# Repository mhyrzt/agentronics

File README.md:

# agentronics
Revisiting electronics and embedded systems with old sparks, new circuits, questionable ideas, and a few AI agents running around the lab with a suspicious amount of confidence.

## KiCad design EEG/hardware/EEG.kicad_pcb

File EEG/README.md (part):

# Building a four-channel EEG: from electrodes to wireless samples

An EEG board has an unusual job: preserve a very small voltage difference while its own processor, radio and power supply are doing comparatively noisy work. Understanding this board starts with that tension. The ADC needs quiet inputs and a stable reference; the radio needs bursts of current; the battery has a voltage that changes as it discharges. Each circuit exists to manage part of that problem.

This README walks through **Revision B**, a four-channel, battery-powered learning prototype built in KiCad 9. The PCB is 60 × 60 mm with two copper layers. You can follow the explanation alongside the [annotated schematic overview](exports/previews/EEG.svg) and use the component references, such as **R1** or **U1**, to find the actual parts.

**Current status:** the schematic and routed PCB pass CAD checks, but the board has not been assembled or electrically tested. Firmware is still to be written. The explanations below describe design intent and calculations, not measured performance or qualification for connection to a person. Start with simulated signals on the bench.

Read in order to follow the circuit, or jump to [inputs](#why-the-inputs-contain-more-than-a-wire), [ADC support](#why-use-a-dedicated-adc-instead-of-the-processors-adc), [bias](#why-there-is-a-separate-bias-circuit), [power](#two-supply-rails-two-different-priorities), [external controller](#the-external-controller-coordinates-acquisition), [bench bring-up](#bringing-the-board-to-life-on-the-bench) or [project files](#find-the-design-files-and-open-them).

If you are new to schematics, **R** means resistor, **C** capacitor, **D** diode, **U** integrated circuit/module, **J** connector, **L** inductor, **F** fuse and **SW** switch. The following number identifies that particular part; it does not describe its value. For example, R1 is a 10 kΩ resistor. Net names such as `CH1_ADC` identify electrical connections even when the drawing does not show a continuous wire between pages.

## Start with the journey of one sample

Suppose channel 1's electrode voltage changes relative to the reference electrode. That difference passes through the input network, reaches the ADC, becomes a signed digital sample, and eventually leaves the radio as part of a packet. The external processor handles the packets; the ADS1299 performs the analog acquisition. Revision B has no onboard ESP32, antenna or RF design.

```mermaid
flowchart LR
    E["CH1–CH4 electrodes + REF"] --> I["Input resistors, clamps and filters"]
    I --> A["U1 ADS1299-4\nGain + simultaneous conversion"]
    A -->|"SPI cable; DRDY timing"| M["External ESP32 development board\nBuffer and packetize"]
    M -->|"Wi-Fi WebSocket — firmware pending"| H["Receiver\nDisplay and analysis"]
    A --> B["Bias amplifier + R11/R12"]
    B -->|"BIAS electrode"| E
```

*The actual KiCad overview page maps the same functional blocks. Click the image for the vector version.*

The schematic pages follow the same division: **Inputs** prepares the electrode signals, **Frontend** contains the ADC and its support circuits, **Power** generates the supply rails, and **Controller** contains the external-board cable interface, and **USB** contains the bench input and analog boost. The root page is the map between them.

## What does a channel actually measure?

A voltage is always measured between two points. In this board, each ADC channel receives a positive input and a negative input:

$$
V_{\mathrm{diff},i}
= V_{P,i} - V_{N,i},
\qquad i \in \{1,2,3,4\}
$$

Here $V_{P,i}$ is the voltage at channel $i's positive ADC input (`CH1_ADC` through `CH4_ADC`), and $V_{N,i}$ is the voltage at its negative ADC input (`CH1_N` through `CH4_N`). These indexed mathematical symbols keep schematic net names separate from LaTeX subscripts.

Each channel's signed digital sample represents this differential voltage, scaled by the configured gain and ADC reference.

The four negative inputs originate at the same external **REF** electrode, but each has its own resistor/clamp branch. This is a shared-reference arrangement: the board measures four electrode-to-reference differences. It does not provide four separately accessible negative-electrode connections. Interference or movement at REF can therefore appear in several channels at once.

As a thought experiment, 2.500010 V at one input and 2.500000 V at the other produce a differential voltage of just 10 µV, despite both inputs sitting near 2.5 V. This is why the board needs both precise differential measurement and control of the average input voltage. These are illustrative numbers, not electrode voltages measured on this board.

Three different kinds of “reference” appear in this project. Keeping them distinct makes the rest of the schematic easier to read.

| Name                                   | What it does here                                                                               |
|----------------------------------------|-------------------------------------------------------------------------------------------------|
| **REF electrode**                      | The external comparison point for the four signal measurements.                                 |
| **ADC voltage reference, VREFP/VREFN** | Sets the conversion scale: how analog voltage becomes a digital number.                         |
| **BIAS electrode**                     | Carries the bias amplifier's driven output, intended to help control input common-mode voltage. |
| **GND**                                | The electronics' shared supply return. It is not an electrode pin on J1.                        |

Differential voltage and **common-mode voltage** are also different. If both ADC inputs rise by the same amount, their difference stays constant, but their average voltage rises. A differential ADC can reject much of that shared disturbance only while both inputs remain within their allowed operating range. Biasing and electrode impedance matter even when the desired difference is tiny.

## Why the inputs contain more than a wire

Open the **Inputs** sheet and trace channel 1. The following is a simplified electrical view; the clamp symbols stand for the paired diodes connected to GND and A5V.

```text
CH1 electrode ── R1 10k ──●── R2 10k ──●── CH1_ADC / ADC IN1P
                         │             │
                    D1 rail clamp      │
                                       C1 4.7nF
REF electrode ── R9 10k ──●── R10 10k ─●── CH1_N   / ADC IN1N
                         │
                    D5 rail clamp
```

*Inputs sheet, callout I1: trace CH1_E and REF_E through the two branches to the ADC pair. Click the image for the vector version.*

<details>
<summary>Open the full annotated Inputs schematic page</summary>

</details>

The signal still reaches the ADC through resistors. The diodes sit on branches, and C1 connects across the two ADC inputs. Those positions explain their jobs.

### The resistors limit current, but they have a cost

R1 and R9 sit between the external connector and the clamp nodes. They reduce the current that can flow toward a conducting clamp during an excursion. R2 and R10 add resistance between those nodes and the ADC and participate in the differential filter.

Increasing resistance is not a free improvement. It also adds thermal noise, increases the offset caused by leakage current, and changes the response when combined with electrode impedance and capacitance. The two 10 kΩ resistors per branch are this revision's starting choice, to be evaluated on the bench. These networks are not certified patient, defibrillator or ESD protection.

The same pattern repeats across all four channels:

| Channel | Positive branch | Reference branch | Clamps | Differential capacitor |
|---------|-----------------|------------------|--------|------------------------|
| 1       | R1, R2          | R9, R10          | D1, D5 | C1                     |
| 2       | R3, R4          | R33, R34         | D2, D7 | C2                     |
| 3       | R5, R6          | R35, R36         | D3, D8 | C3                     |
| 4       | R7, R8          | R37, R38         | D4, D9 | C4                     |

### Why BAV199 diodes?

Normally the clamp diodes should contribute very little current to the input. Leakage matters because current through an impedance produces a voltage error: $V_{\mathrm{error}} = I_{\mathrm{leak}} R$. For example:

$$
V_{\mathrm{error}}
= (1\,\mathrm{nA})(20\,\mathrm{k}\Omega)
= 20\,\mu\mathrm{V}
$$
 That is an illustrative calculation, not a prediction of this board's leakage.

BAV199 is chosen for its low leakage. Each package contains two series-connected diodes, with their shared junction accessible at pin 3. Here, pin 1 goes to GND, pin 2 to A5V, and pin 3 to the clamp node. A large excursion can forward-bias one diode toward the corresponding rail. This is a leakage-conscious clamp choice, not a guarantee of transient survival; the rails also need to accommodate injected current. See [Nexperia's BAV199 data sheet](https://assets.nexperia.com/documents/data-sheet/BAV199.pdf).

### Why put C1 between the inputs?

C1–C4 provide a path for higher-frequency **differential** disturbances between the positive and negative inputs. Using one capacitor across the pair also avoids making this circuit depend on matching two separate capacitors to ground. It does not eliminate common-mode interference.

For a simplified small-signal model, with nonconducting clamps and negligible external source impedance, the resistance seen by C1 is the sum of both branches:

$$
\begin{aligned}
R_{\mathrm{diff}}
&= (10 + 10 + 10 + 10)\,\mathrm{k}\Omega
= 40\,\mathrm{k}\Omega \\
C_{\mathrm{diff}} &= 4.7\,\mathrm{nF} \\
f_c &\approx \frac{1}{2\pi R_{\mathrm{diff}} C_{\mathrm{diff}}} \\
&= \frac{1}{2\pi (40\times10^3)(4.7\times10^{-9})}\,\mathrm{Hz}
\approx 847\,\mathrm{Hz}
\end{aligned}
$$

This pole is well above the proposed 0.5–40 Hz application band. It is an input high-frequency attenuation stage, not the finished EEG bandpass or a complete anti-aliasing guarantee. Electrode impedance and parasitics change the actual response. The ADC's conversion/decimation behavior and later firmware filtering must be considered together.

C0G dielectric was selected for C1–C4 to keep the filter capacitance relatively stable. The larger supply capacitors use other dielectrics because their job is storing and delivering charge rather than setting this small-signal filter value.

## Why use a dedicated ADC instead of the processor's ADC?

**U1, ADS1299-4PAG**, combines four simultaneous conversion channels with programmable gain, a voltage reference, test facilities and a bias amplifier. That integration lets this project focus on electrode interfaces, supplies, layout and acquisition software rather than designing a separate precision amplifier chain for each channel. The four-channel variant matters: its pin usage and sample format must match the firmware. See the [TI ADS1299 family data sheet](https://www.ti.com/lit/ds/symlink/ads1299.pdf).

*Frontend sheet, F1: the input pairs enter U1 at left; control and sample-transfer signals are at right. Click the image for the vector version.*

A **24-bit** output is a number format, not a promise of 24 useful bits of accuracy. Noise, offsets, gain error, the voltage reference and the input circuit determine what changes can actually be resolved. Likewise, programmable gain magnifies electrode offsets along with the wanted signal; using maximum gain immediately can cause clipping.

For that reason, initial firmware should use a modest gain, check raw offsets and saturation, and test known signals before choosing its operating gain. A smooth-looking plotted trace is weak evidence if the raw samples are already clipped or missing.

### Why all the capacitors around U1?

Some support the chip's internal circuits; others keep its external supplies locally steady. Their identical capacitor symbols hide very different responsibilities.

| Parts                       | Connection / purpose in this board                              |
|-----------------------------|-----------------------------------------------------------------|
| C6, 100 µF                  | VCAP1 support capacitor; polarized tantalum, positive at VCAP1. |
| C7, 1 µF                    | VCAP2 support capacitor.                                        |
| C8, 1 µF, and C9, 100 nF    | VCAP3 support capacitors.                                       |
| C10, 1 µF                   | VCAP4 support capacitor.                                        |
| C11, 10 µF, and C12, 100 nF | Bypass the conversion reference between VREFP and VREFN/GND.    |
| C13–C17, 1 µF each          | Local analog-supply bypass at the ADC supply groups.            |
| R14, 0 Ω, and C18, 1 µF     | Feed and bypass the separate A5V_CP supply branch.              |
| C19, 10 µF, and C20, 100 nF | Additional analog-rail bulk/local bypass.                       |
| C21, 1 µF, and C22, 100 nF  | Bypass the ADC's 3.3 V digital supply.                          |

*Frontend sheet, F2: VCAP networks and the VREFP bypass are different support circuits. Click the image for the vector version.*

<details>
<summary>Open the full annotated Frontend schematic page</summary>

</details>

The VCAP and reference values follow the device's single-supply application circuit; treat those pins according to their specified function rather than as spare power outputs. Local bypass capacitors give changing load currents a short path. A capacitor far away, connected through a long inductive route, cannot serve that job equally well.

R14 is a deliberate removable link. A zero-ohm resistor conducts like a connection but leaves an assembly point for isolating the branch or evaluating a future modification. It does not filter noise by itself.

### Hardware defaults keep startup understandable

The processor takes time to boot. Pull resistors give the ADC's control pins defined levels during that interval: R21/R22 hold RESET/START low, R23 holds chip select high, and R19/R20 select the internal clock and hold PWDN high. R15–R18 define the unused ADC GPIO inputs.

Firmware must then deliberately initialize the ADC. The unused SRB reference switches remain disabled because this board routes its reference through four external branches. Clock output stays disabled because the external clock pin is grounded. Changing register settings can make correctly wired hardware behave incorrectly.

## Why there is a separate bias circuit

A signal can have a small differential voltage and still sit at an unsuitable common-mode voltage. The bias circuit addresses that separate problem. Its intended behavior is a feedback loop: observe selected channel common-mode information, generate a corrective output, and couple that output through the BIAS electrode path.

```text
Selected input common-mode information
                  │
                  v
       ADS1299 internal bias amplifier
                  │ BIAS_OUT
                  ├── R11 499k ── R12 499k ── BIAS electrode
                  │
                  └── [ R13 1M || C5 1nF ] ── BIAS_INV
                              feedback
```

*Frontend sheet, F3: R13 and C5 share both endpoints, forming the parallel feedback network. Click the image for the vector version.*

R13 and C5 are in parallel in the amplifier's feedback path. The resistor provides the resistive feedback path; the capacitor changes the loop's frequency response. Their RC frequency scale is:

$$
f_{\mathrm{RC}} = \frac{1}{2\pi R_{13} C_5}
= \frac{1}{2\pi (1\times10^6)(1\times10^{-9})}\,\mathrm{Hz}
\approx 159\,\mathrm{Hz}
$$

**That is not a measured closed-loop bandwidth**: the channel sensing configuration, amplifier behavior and external electrode/load network also affect the loop.

R11 and R12 total 998 kΩ in series with the driven output, limiting current for a given voltage difference. Having two resistors leaves resistance if one is shorted, but this observation is not a safety qualification. The feedback returns from BIAS_OUT before those resistors; the external electrode path must still be evaluated with a simulated load.

This revision uses the ADC's internal bias reference. BIASREF and unused BIASIN are grounded. Enable the amplifier only after verifying the configuration and checking stability. REF is a measurement input; BIAS is an actively driven output. They are not interchangeable connector pins.

## Two supply rails, two different priorities

The ADC analog circuits need a regulated 5 V rail, while digital logic and the external ESP32 use 3.3 V. Revision B accepts either a protected 2S battery or a 5 V USB-C bench adapter. USB cannot reliably feed the old 5 V LDO directly: the input diode, cable drop and regulator dropout would leave too little headroom. The added boost converts the selected input to nominally 9.04 V for the low-current analog branch, followed by the existing 5 V LDO. The external controller's higher-current supply comes from the separate 3.3 V buck.

```mermaid
flowchart TD
    BAT["J2: protected 2S battery"] --> F["F1 PTC + D6 polarity diode"]
    USB["J6: 5 V USB-C bench supply"] --> UF["F2 PTC + D10 diode"]
    F --> OR["BAT_PROTECTED: diode OR"]
    UF --> OR
    OR --> J["J4: removable enable shunt"]
    J --> SW["BAT_SW"]
    SW --> BUCK["U3 AP63203 + L1: 3.3 V buck"]
    BUCK --> DV["ADC digital + automatic power to external ESP32"]
    SW --> BOOST["U5 AP3031 + L2/D11: analog boost"]
    BOOST --> LDO["U4 LP2985-N: regulated 5 V"]
    LDO --> AV["A5V: ADC analog circuitry"]
    SW --> SENSE["VIN_SENSE: selected input voltage"]
    USB --> PRESENT["USB_PRESENT: identify USB bench mode"]
```

Both sources share ground. D6/D10 steer normal source current and resist backfeed; they do not isolate a USB-connected computer or supply. If both sources are present, the higher battery voltage normally supplies the board. Connecting USB still creates a wired ground connection, so USB operation is for bench fixtures with electrode cables disconnected. There is no battery charging or USB data connection on this EEG board.

### Fuses, source diodes and J4: different jobs

*Power sheet, P1: the battery passes through three separate functions before reaching BAT_SW. Click the image for the vector version.*

**F1 and F2**, 0.75 A-hold PTCs, increase resistance when sufficiently heated by excess current. Its response depends on current and temperature; it is not a precise 0.75 A electronic cutoff. The pack still requires its own protection.

**D6**, an SS14 Schottky diode, blocks a reversed battery connection; **D10** provides the USB branch of the diode OR. Its forward drop costs some voltage and dissipates heat. That loss needs to be included when checking regulator headroom at low battery voltage.

**J4** turns the downstream circuit on when a suitably rated shunt joins its two pins. Removing it disconnects BAT_SW, but the battery-side parts remain connected to the pack. Unplugging the pack is the master disconnect. There is no onboard charger: remove the pack for compatible offboard charging.

### Why the 3.3 V regulator switches

A linear regulator converting roughly 7.4 V to 3.3 V would turn the voltage difference into heat. As an illustration, at 100 mA:

$$
\begin{aligned}
P_{\mathrm{loss}} &\approx (V_{\mathrm{in}}-V_{\mathrm{out}}) I_{\mathrm{load}} \\
&= (7.4-3.3)\,\mathrm{V}\times0.1\,\mathrm{A}
= 0.41\,\mathrm{W}
\end{aligned}
$$

That is not a measured radio load. It explains the motivation for **U3, AP63203**, a fixed-3.3 V switching buck. Its switching stage transfers energy through **L1, 4.7 µH**, and the output capacitors. The tradeoff is switching ripple and fast current loops that need attention in layout and measurement. See the [AP63203 family data sheet](https://www.diodes.com/datasheet/download/AP63200-AP63201-AP63203-AP63205.pdf).

*Power sheet, P2: identify the bootstrap capacitor, inductor, output capacitors and feedback connection. Click the image for the vector version.*

C28/C29 bypass its input. C30 is the bootstrap capacitor between BST and SW, supporting the high-side gate-drive circuit. C31/C32 store charge at the output, and FB senses the resulting 3.3 V rail. L1's saturation and current ratings provide design margin; a high inductor current rating does not mean the EEG board normally draws that current.

### Why the power LED has its own resistor

**D13** is a small green 0805 LED; **R45** limits its current from the digital 3.3 V rail. The branch is wired as:

```text
3V3 ── R45 (1 kΩ) ── D13 anode → cathode ── GND
```

Using the [Kingbright datasheet](https://www.kingbrightusa.com/images/catalog/spec/apt2012lzgck.pdf) nominal forward voltage of 2.65 V at its 2 mA test current gives an illustrative estimate:

$$
I_{\mathrm{LED}} \approx \frac{V_{\mathrm{3V3}}-V_F}{R_{45}}
= \frac{3.3\,\mathrm{V}-2.65\,\mathrm{V}}{1\,\mathrm{k}\Omega}
= 0.65\,\mathrm{mA}
$$

The actual forward voltage changes with current and temperature, so measure the fitted LED current and brightness on the bench. A steady indicator avoids adding a blinking load. Its extra current still reduces battery runtime slightly.

The LED indicates **3V3 present**, whether powered from the battery or USB-C through J4. It does not confirm A5V, correct ADC configuration, safe electrode connection or sufficient battery charge. It is not a charger indicator. If an external board back-powers 3V3 through J5 pin 2, the LED may also light. Disconnect that power cable before powering the external board from its own USB.

### What the USB-C circuit does

J6 is a GCT USB4105 receptacle. R39/R40 each provide a separate 5.1 kΩ sink termination on CC1/CC2, so a suitable USB-C source can detect the connection in either orientation. F2 supplies the input's overcurrent response, D10 steers its power into the shared supply node, and D12 is a VBUS transient suppressor. A connector's current rating does not negotiate source current.

Use a dedicated **5 V USB-C bench adapter rated at least 1 A**, with a suitable cable; verify its behavior under the actual load. This revision does not implement USB enumeration, Type-C advertised-current decoding or Power Delivery, and is not intended to draw its full load from an arbitrary computer USB port. D+/D− and SBU pins are explicitly unconnected. Program the external ESP32 through that development board's own USB port, following the power-link rule below.

*USB sheet: U1 explains the CC terminations; U2 identifies the analog boost and the USB ground boundary. Click for the vector drawing.*

### Why add a boost before the analog regulator?

The battery supply is above 5 V, but a USB input after a diode can be below it. The AP3031 boost, U5, provides headroom for the analog LDO in both cases. It supplies the ADC analog branch, not the external ESP32. L2 stores energy, D11 rectifies the switching output, C37 bypasses the input and C38 supports the output. R41/R42 set the nominal voltage using the boost's 0.2 V feedback reference:

$$
V_{\mathrm{BOOST}} = V_{\mathrm{FB}}\left(1+\frac{R_{41}}{R_{42}}\right)
= 0.2\,\mathrm{V}\left(1+\frac{442\,\mathrm{k}\Omega}{10\,\mathrm{k}\Omega}\right)
= 9.04\,\mathrm{V}
$$

That result is nominal: feedback-reference tolerance, resistor tolerance and load affect the actual voltage. The extra switching stage adds components and another noise source, so its loop is kept away from the electrode section. The LDO then drops the boosted voltage to 5 V. Startup, boost stability, analog ripple and noise must be measured. The [AP3031 data sheet](https://www.diodes.com/assets/Datasheets/AP3031.pdf) includes voltage-divider boost applications as well as its LED-driver applications.

### Why the analog rail uses a linear regulator

**U4, LP2985-N**, makes A5V from BOOST9V. The LDO adds a linear stage after the boost, at the cost of heat approximately proportional to voltage drop times load current. C33 bypasses its input, C34 bypasses its internal noise-related node, and C35/C36 support the output.

*Power sheet, P3: follow BOOST9V to the LDO and A5V; C34 and C35 serve different purposes. Click the image for the vector version.*

<details>
<summary>Open the full annotated Power schematic page</summary>

</details>

The output capacitor is part of the regulator's stability system. TI documents different capacitance/ESR considerations for legacy and newer silicon; the installed device and effective ceramic capacitance must be checked rather than assuming any nominal 10 µF capacitor is suitable. Startup, load steps, ripple and oscillation are bench checks still to perform. See [TI's LP2985-N data sheet](https://www.ti.com/lit/ds/symlink/lp2985-n.pdf).

### Why capacitor voltage ratings exceed the rail voltage

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
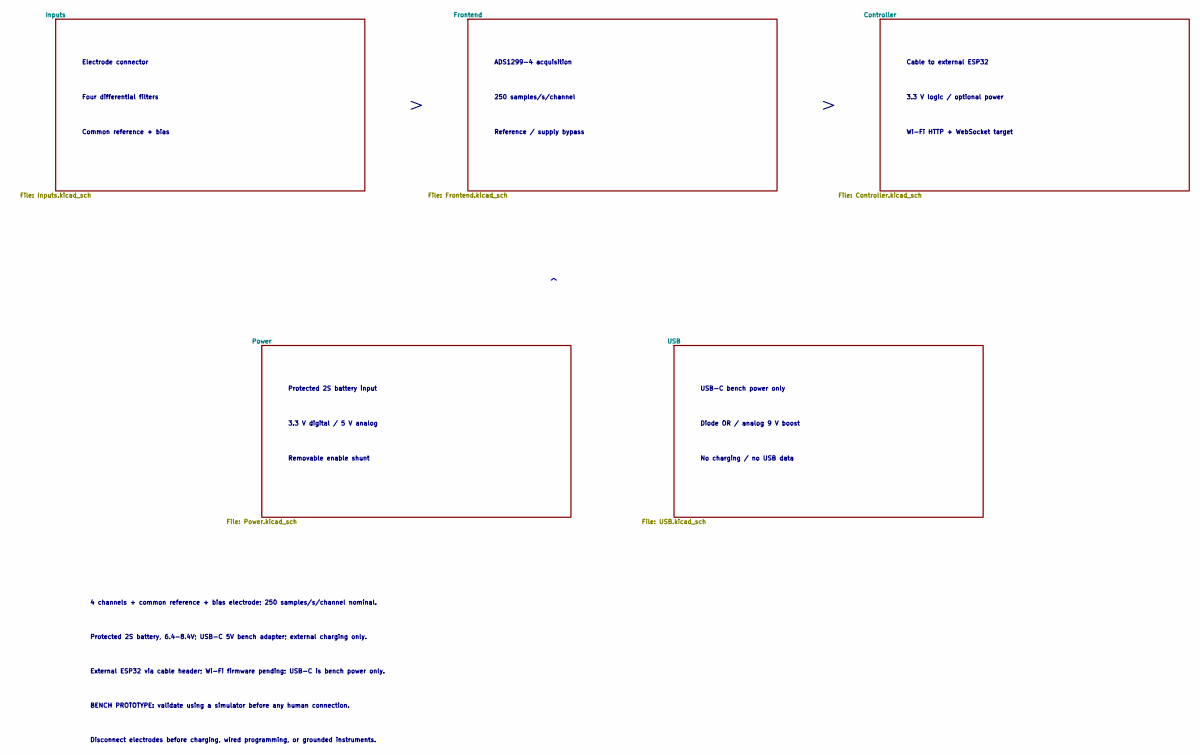
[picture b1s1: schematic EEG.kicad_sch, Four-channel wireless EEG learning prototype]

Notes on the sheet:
Electrode connector
Four differential filters
Common reference + bias
ADS1299-4 acquisition
250 samples/s/channel
Reference / supply bypass
Protected 2S battery input
3.3 V digital / 5 V analog
Removable enable shunt
USB-C bench power only
Diode OR / analog 9 V boost
No charging / no USB data
Cable to external ESP32
3.3 V logic / optional power
Wi-Fi HTTP + WebSocket target
4 channels + common reference + bias electrode; 250 samples/s/channel nominal.
Protected 2S battery, 6.4-8.4V; USB-C 5V bench adapter; external charging only.
External ESP32 via cable header; Wi-Fi firmware pending; USB-C is bench power only.
BENCH PROTOTYPE: validate using a simulator before any human connection.
Disconnect electrodes before charging, wired programming, or grounded instruments.

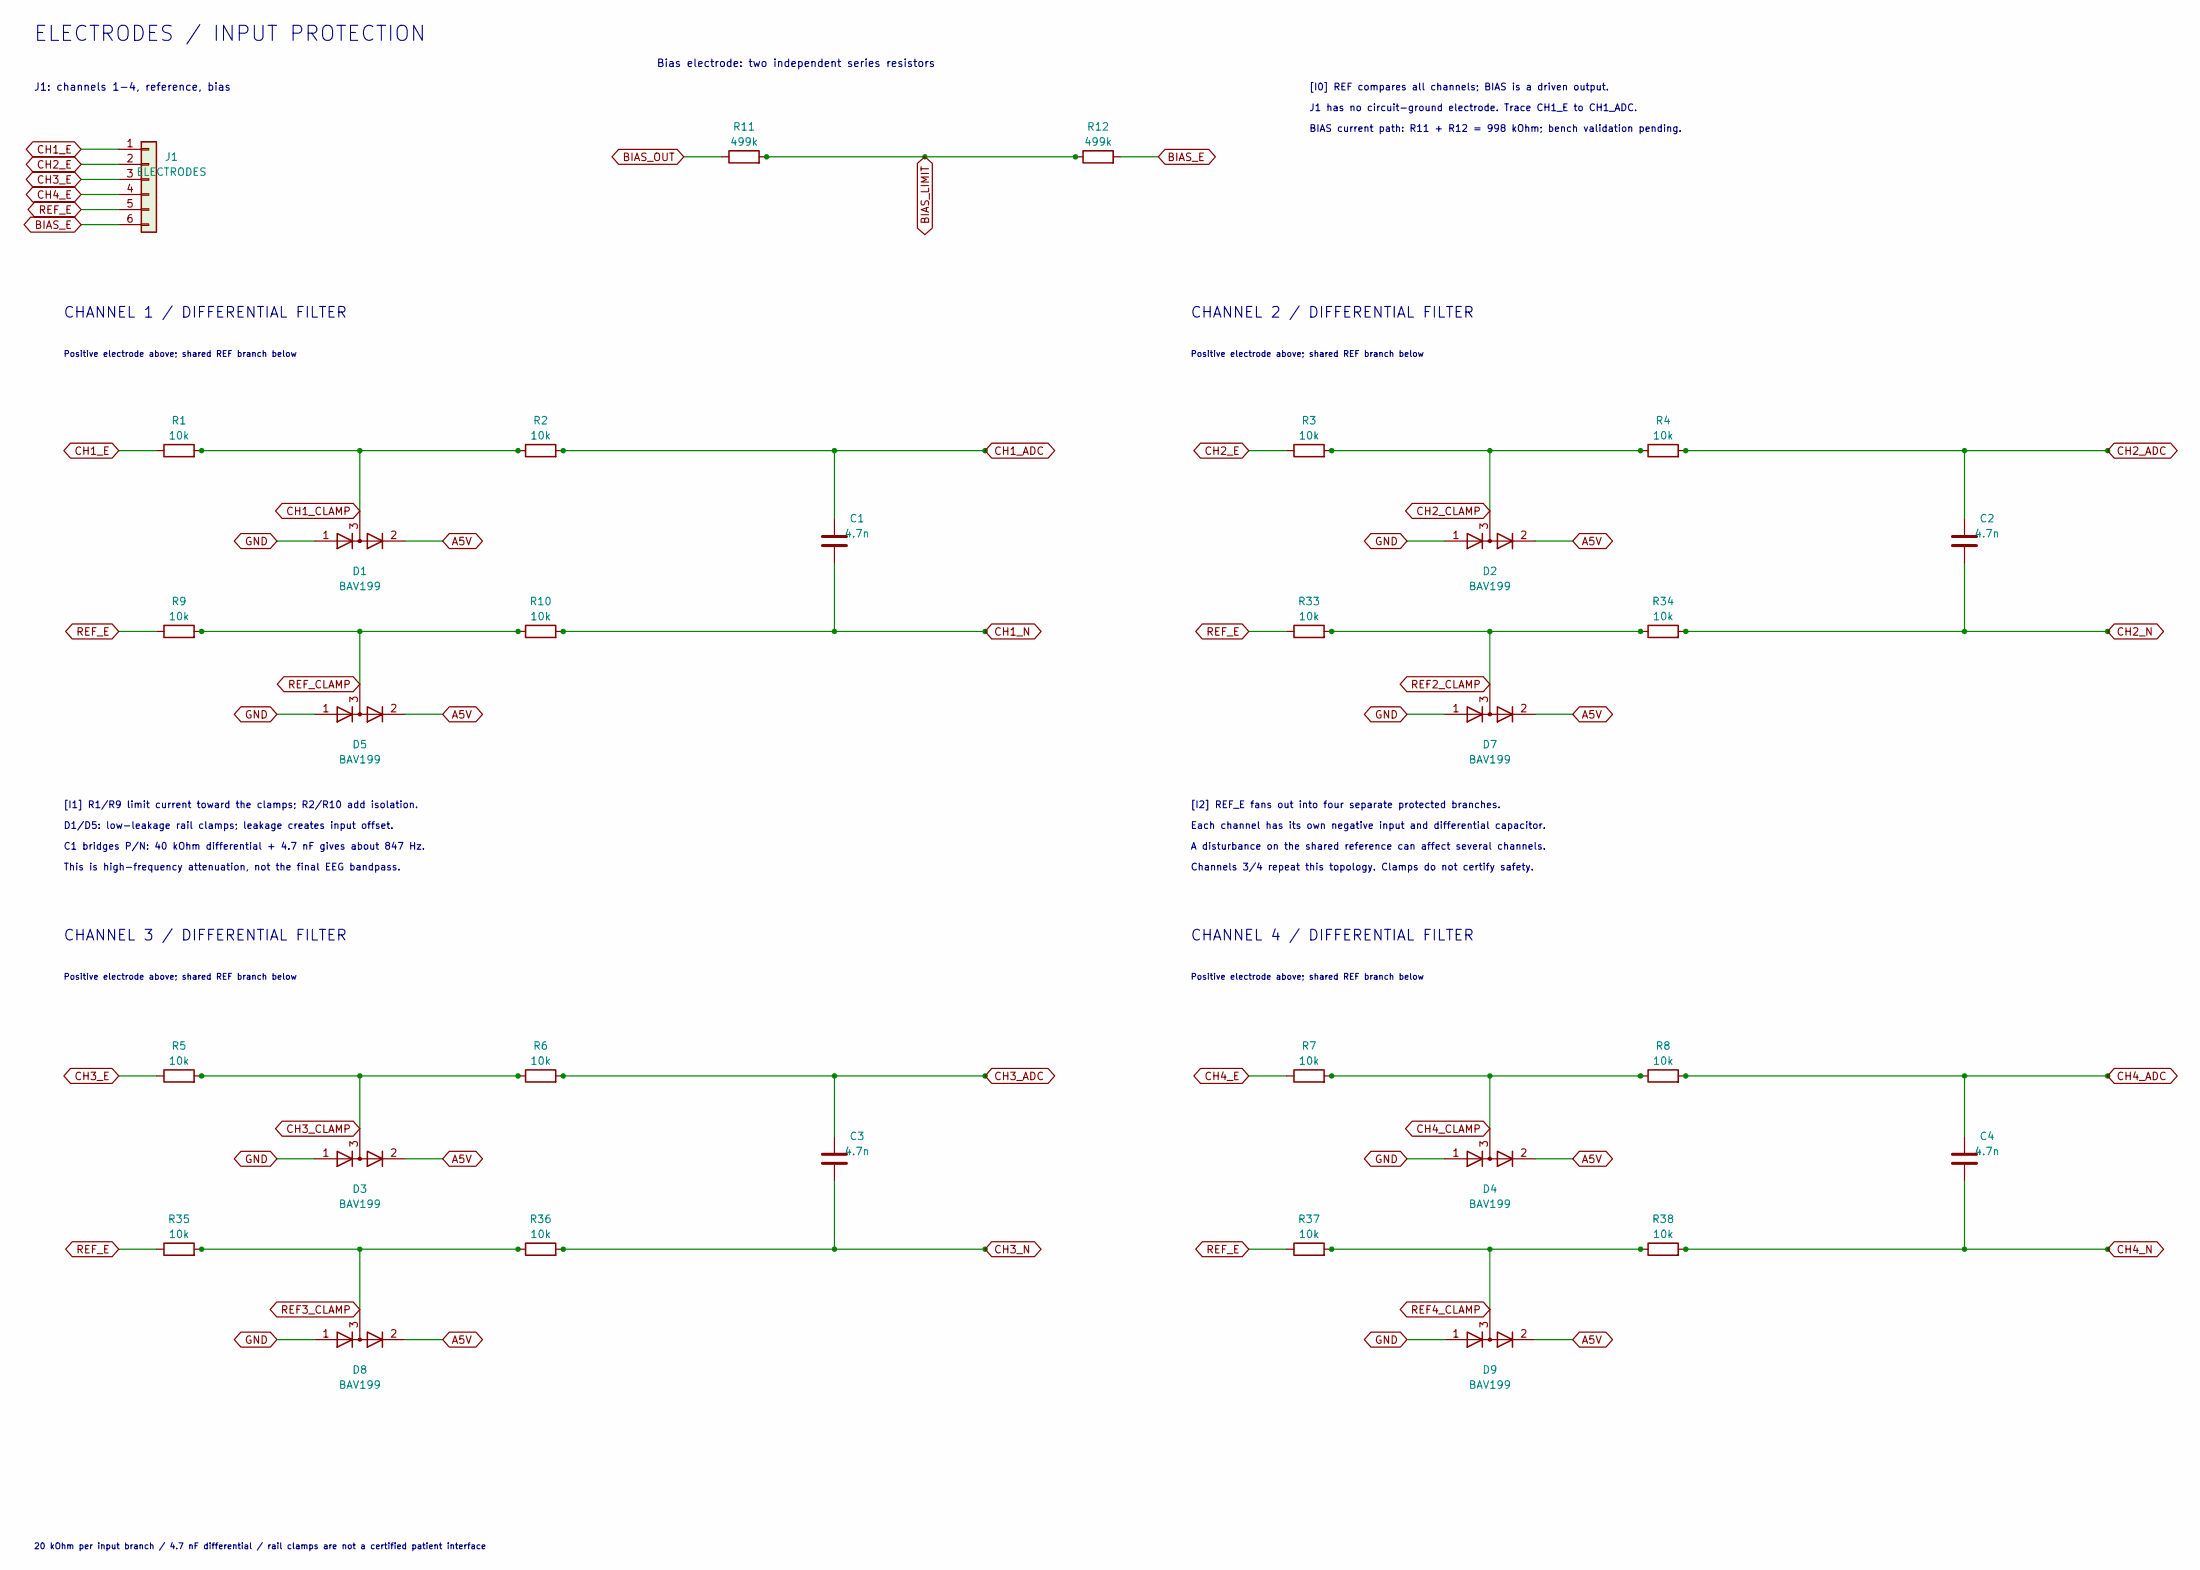
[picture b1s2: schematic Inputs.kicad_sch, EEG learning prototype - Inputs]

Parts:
C1, C2, C3, C4: 4.7n; C_0805_2012Metric; MPN GRM21A5C1H472JA01D
D1, D2, D3, D4, D5, D7, D8, D9: BAV199; SOT-23; MPN BAV199,215
J1: ELECTRODES; JST_XH_B6B-XH-A_1x06_P2.50mm_Vertical; MPN B6B-XH-A
R1, R2, R3, R4, R5, R6, R7, R8, R9, R10, R33, R34, R35, R36, R37, R38: 10k; R_0805_2012Metric; MPN RC0805FR-0710KL
R11, R12: 499k; R_0805_2012Metric; MPN RC0805FR-07499KL

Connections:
A5V: D1.2 (K2), D2.2 (K2), D3.2 (K2), D4.2 (K2), D5.2 (K2), D7.2 (K2), D8.2 (K2), D9.2 (K2); also elsewhere on the board
BIAS_E: J1.6, R12.2
BIAS_LIMIT: R11.2, R12.1
BIAS_OUT: R11.1; also elsewhere on the board
CH1_ADC: C1.1, R2.2; also elsewhere on the board
CH1_CLAMP: D1.3 (K1/A2), R1.2, R2.1
CH1_E: J1.1, R1.1
CH1_N: C1.2, R10.2; also elsewhere on the board
CH2_ADC: C2.1, R4.2; also elsewhere on the board
CH2_CLAMP: D2.3 (K1/A2), R3.2, R4.1
CH2_E: J1.2, R3.1
CH2_N: C2.2, R34.2; also elsewhere on the board
CH3_ADC: C3.1, R6.2; also elsewhere on the board
CH3_CLAMP: D3.3 (K1/A2), R5.2, R6.1
CH3_E: J1.3, R5.1
CH3_N: C3.2, R36.2; also elsewhere on the board
CH4_ADC: C4.1, R8.2; also elsewhere on the board
CH4_CLAMP: D4.3 (K1/A2), R7.2, R8.1
CH4_E: J1.4, R7.1
CH4_N: C4.2, R38.2; also elsewhere on the board
GND: D1.1 (A1), D2.1 (A1), D3.1 (A1), D4.1 (A1), D5.1 (A1), D7.1 (A1), D8.1 (A1), D9.1 (A1); also elsewhere on the board
REF2_CLAMP: D7.3 (K1/A2), R33.2, R34.1
REF3_CLAMP: D8.3 (K1/A2), R35.2, R36.1
REF4_CLAMP: D9.3 (K1/A2), R37.2, R38.1
REF_CLAMP: D5.3 (K1/A2), R9.2, R10.1
REF_E: J1.5, R9.1, R33.1, R35.1, R37.1

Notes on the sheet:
ELECTRODES / INPUT PROTECTION
J1: channels 1-4, reference, bias
Bias electrode: two independent series resistors
CHANNEL 1 / DIFFERENTIAL FILTER
Positive electrode above; shared REF branch below
CHANNEL 2 / DIFFERENTIAL FILTER
CHANNEL 3 / DIFFERENTIAL FILTER
CHANNEL 4 / DIFFERENTIAL FILTER
20 kOhm per input branch / 4.7 nF differential / rail clamps are not a certified patient interface
[I0] REF compares all channels; BIAS is a driven output.
J1 has no circuit-ground electrode. Trace CH1_E to CH1_ADC.
BIAS current path: R11 + R12 = 998 kOhm; bench validation pending.
[I1] R1/R9 limit current toward the clamps; R2/R10 add isolation.
D1/D5: low-leakage rail clamps; leakage creates input offset.
C1 bridges P/N: 40 kOhm differential + 4.7 nF gives about 847 Hz.
This is high-frequency attenuation, not the final EEG bandpass.
[I2] REF_E fans out into four separate protected branches.
Each channel has its own negative input and differential capacitor.
A disturbance on the shared reference can affect several channels.
Channels 3/4 repeat this topology. Clamps do not certify safety.

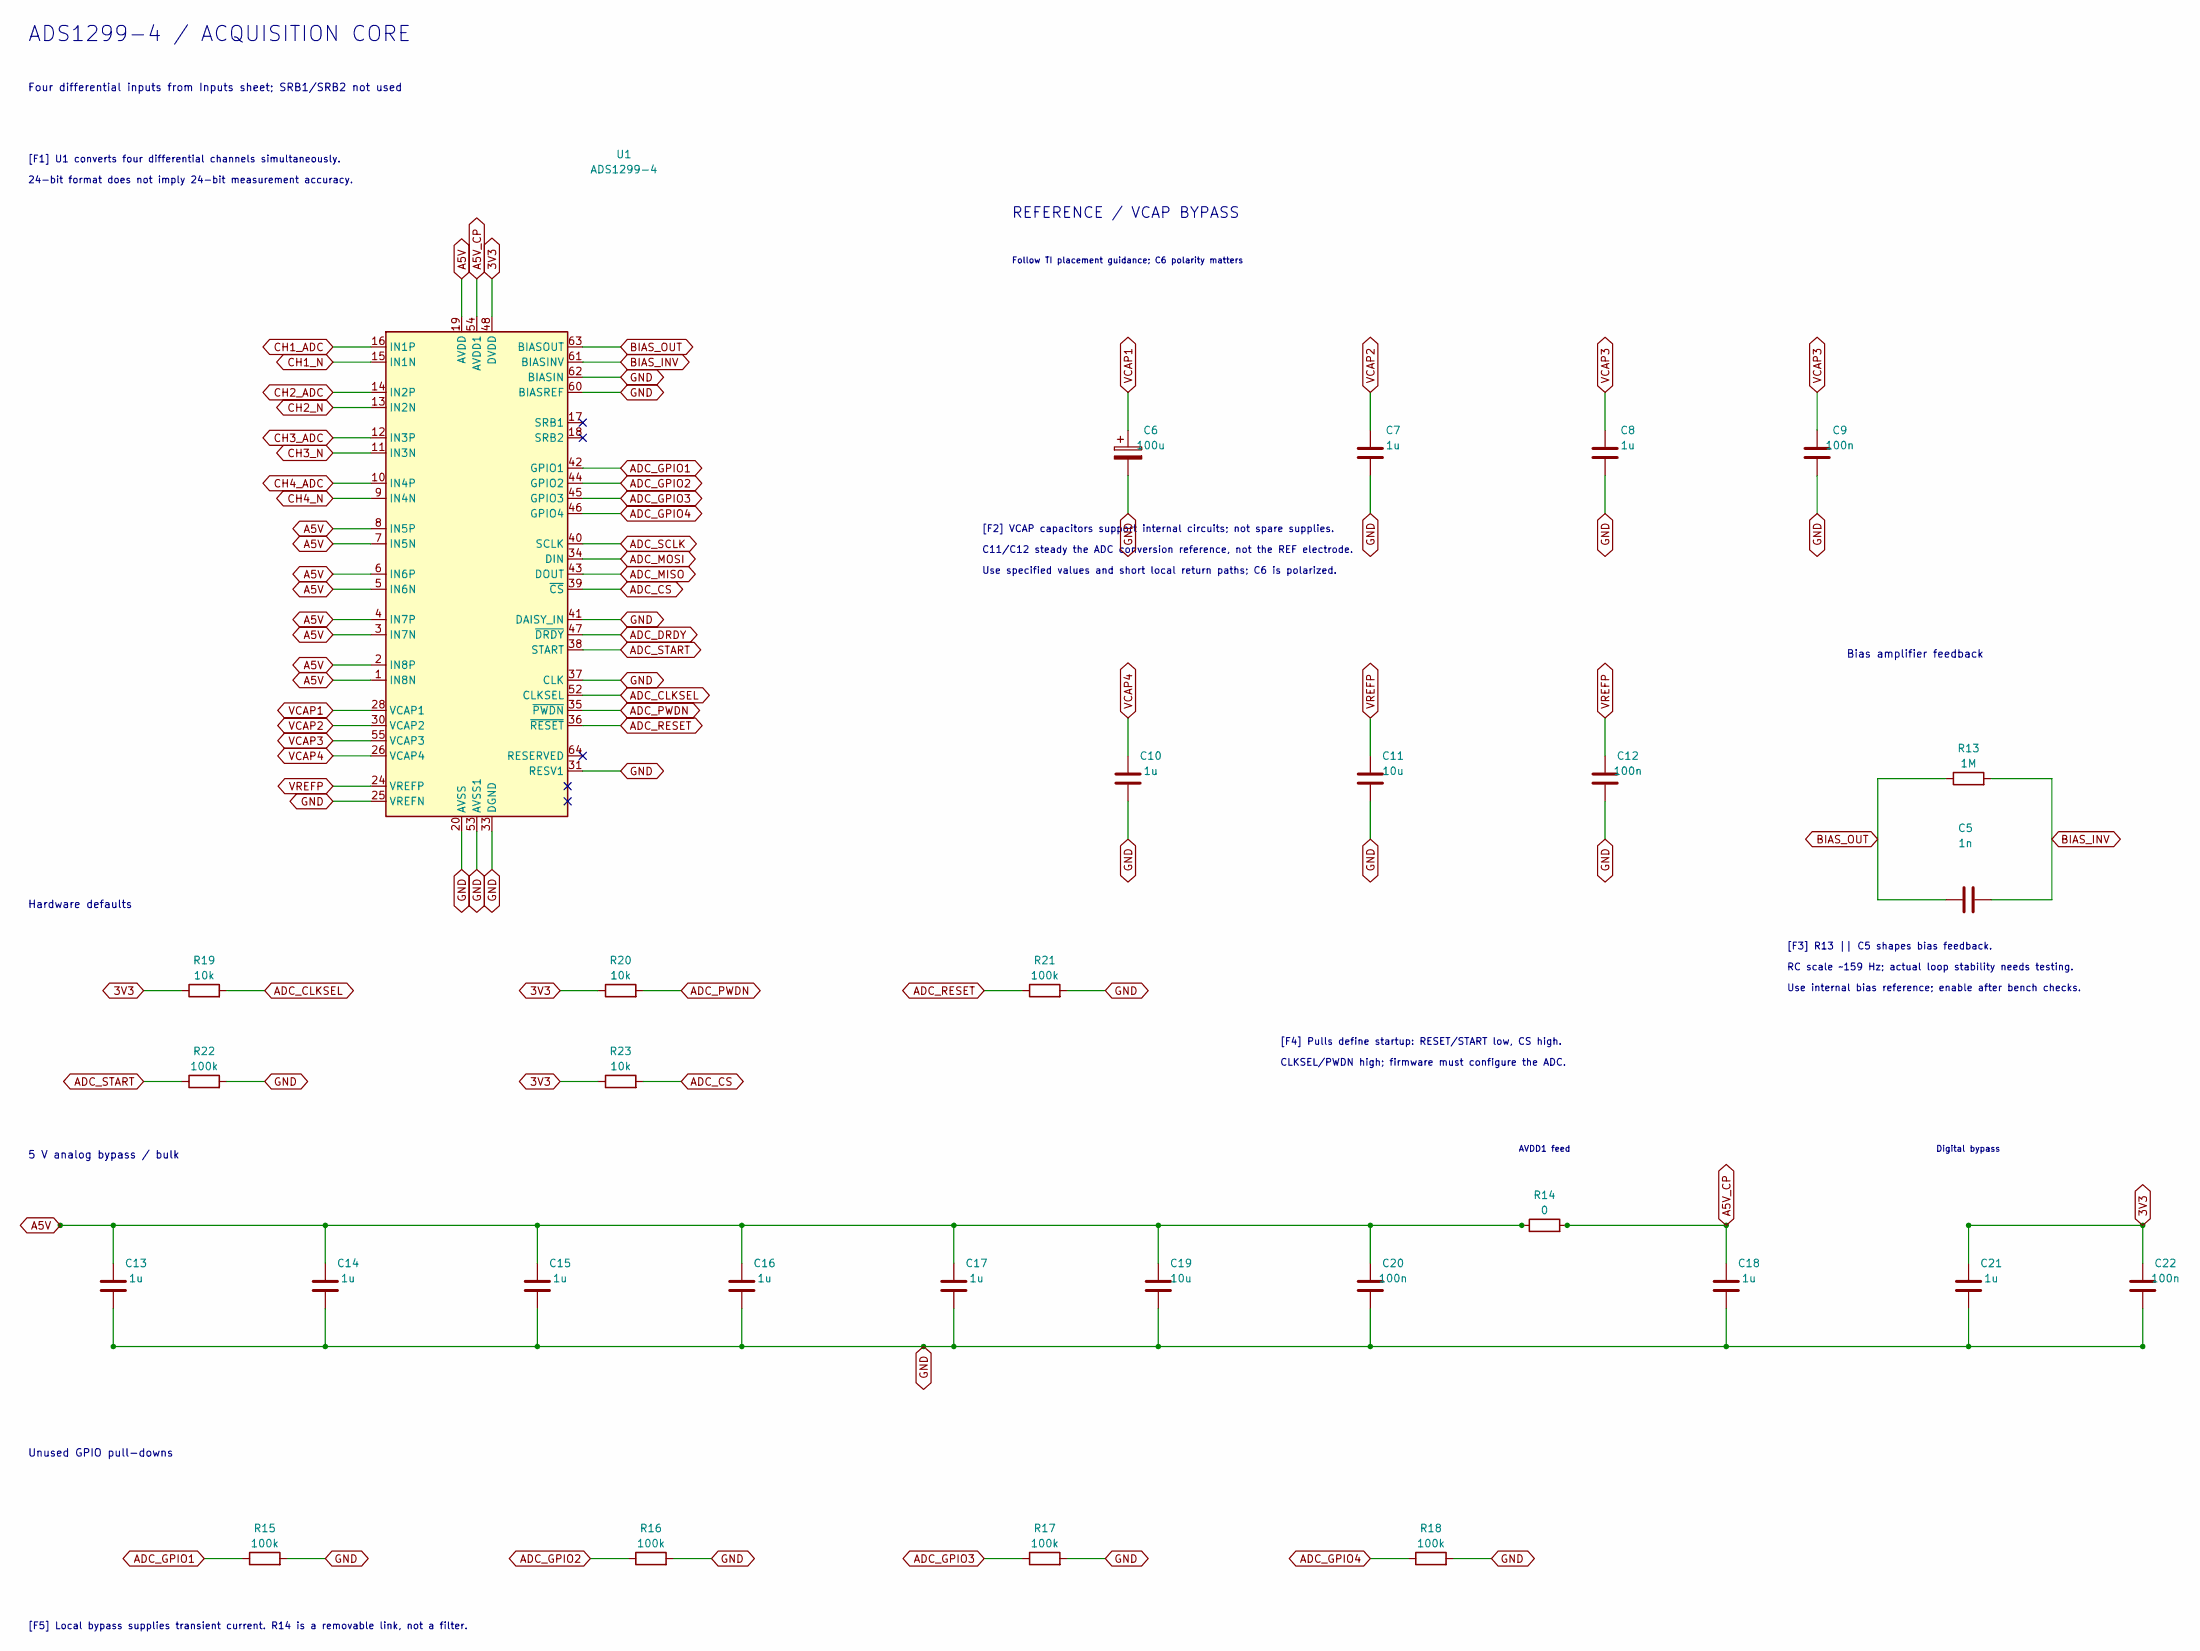
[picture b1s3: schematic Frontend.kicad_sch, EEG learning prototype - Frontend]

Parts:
C5: 1n; C_0805_2012Metric; MPN GRM21A5C1H102JA01D
C6: 100u; CP_EIA-7343-31_Kemet-D; MPN T491D107K010AT
C7, C8, C10, C13, C14, C15, C16, C17, C18, C21: 1u; C_0805_2012Metric; MPN GRM21BR71E105KA99L
C9, C12, C20, C22: 100n; C_0805_2012Metric; MPN GRM21BR71H104KA01L
C11, C19: 10u; C_1206_3216Metric; MPN GRM31CR71C106KA12L
R13: 1M; R_0805_2012Metric; MPN RC0805FR-071ML
R14: 0; R_0805_2012Metric; MPN RC0805JR-070RL
R15, R16, R17, R18, R21, R22: 100k; R_0805_2012Metric; MPN RC0805FR-07100KL
R19, R20, R23: 10k; R_0805_2012Metric; MPN RC0805FR-0710KL
U1: ADS1299-4; TQFP-64_10x10mm_P0.5mm; MPN ADS1299-4PAG

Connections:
3V3: C21.1, C22.1, R19.1, R20.1, R23.1, U1.48 (DVDD), U1.50 (DVDD); also elsewhere on the board
A5V: C13.1, C14.1, C15.1, C16.1, C17.1, C19.1, C20.1, R14.1, U1.1 (IN8N), U1.2 (IN8P), U1.3 (IN7N), U1.4 (IN7P), U1.5 (IN6N), U1.6 (IN6P), U1.7 (IN5N), U1.8 (IN5P), U1.19 (AVDD), U1.21 (AVDD), U1.22 (AVDD), U1.56 (AVDD), U1.59 (AVDD); also elsewhere on the board
A5V_CP: C18.1, R14.2, U1.54 (AVDD1)
ADC_CLKSEL: R19.2, U1.52 (CLKSEL)
ADC_CS: R23.2, U1.39 (~CS); also elsewhere on the board
ADC_DRDY: U1.47 (~DRDY); also elsewhere on the board
ADC_GPIO1: R15.1, U1.42 (GPIO1)
ADC_GPIO2: R16.1, U1.44 (GPIO2)
ADC_GPIO3: R17.1, U1.45 (GPIO3)
ADC_GPIO4: R18.1, U1.46 (GPIO4)
ADC_MISO: U1.43 (DOUT); also elsewhere on the board
ADC_MOSI: U1.34 (DIN); also elsewhere on the board
ADC_PWDN: R20.2, U1.35 (~PWDN)
ADC_RESET: R21.1, U1.36 (~RESET); also elsewhere on the board
ADC_SCLK: U1.40 (SCLK); also elsewhere on the board
ADC_START: R22.1, U1.38 (START); also elsewhere on the board
BIAS_INV: C5.2, R13.2, U1.61 (BIASINV)
BIAS_OUT: C5.1, R13.1, U1.63 (BIASOUT); also elsewhere on the board
CH1_ADC: U1.16 (IN1P); also elsewhere on the board
CH1_N: U1.15 (IN1N); also elsewhere on the board
CH2_ADC: U1.14 (IN2P); also elsewhere on the board
CH2_N: U1.13 (IN2N); also elsewhere on the board
CH3_ADC: U1.12 (IN3P); also elsewhere on the board
CH3_N: U1.11 (IN3N); also elsewhere on the board
CH4_ADC: U1.10 (IN4P); also elsewhere on the board
CH4_N: U1.9 (IN4N); also elsewhere on the board
GND: C6.2, C7.2, C8.2, C9.2, C10.2, C11.2, C12.2, C13.2, C14.2, C15.2, C16.2, C17.2, C18.2, C19.2, C20.2, C21.2, C22.2, R15.2, R16.2, R17.2, R18.2, R21.2, R22.2, U1.20 (AVSS), U1.23 (AVSS), U1.25 (VREFN), U1.31 (RESV1), U1.32 (AVSS), U1.33 (DGND), U1.37 (CLK), U1.41 (DAISY_IN), U1.49 (DGND), U1.51 (DGND), U1.53 (AVSS1), U1.57 (AVSS), U1.58 (AVSS), U1.60 (BIASREF), U1.62 (BIASIN); also elsewhere on the board
VCAP1: C6.1, U1.28 (VCAP1)
VCAP2: C7.1, U1.30 (VCAP2)
VCAP3: C8.1, C9.1, U1.55 (VCAP3)
VCAP4: C10.1, U1.26 (VCAP4)
VREFP: C11.1, C12.1, U1.24 (VREFP)

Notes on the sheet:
ADS1299-4 / ACQUISITION CORE
Four differential inputs from Inputs sheet; SRB1/SRB2 not used
REFERENCE / VCAP BYPASS
Follow TI placement guidance; C6 polarity matters
Bias amplifier feedback
Hardware defaults
5 V analog bypass / bulk
AVDD1 feed
Digital bypass
Unused GPIO pull-downs
[F1] U1 converts four differential channels simultaneously.
24-bit format does not imply 24-bit measurement accuracy.
[F2] VCAP capacitors support internal circuits; not spare supplies.
C11/C12 steady the ADC conversion reference, not the REF electrode.
Use specified values and short local return paths; C6 is polarized.
[F3] R13 || C5 shapes bias feedback.
RC scale ~159 Hz; actual loop stability needs testing.
Use internal bias reference; enable after bench checks.
[F4] Pulls define startup: RESET/START low, CS high.
CLKSEL/PWDN high; firmware must configure the ADC.
[F5] Local bypass supplies transient current. R14 is a removable link, not a filter.

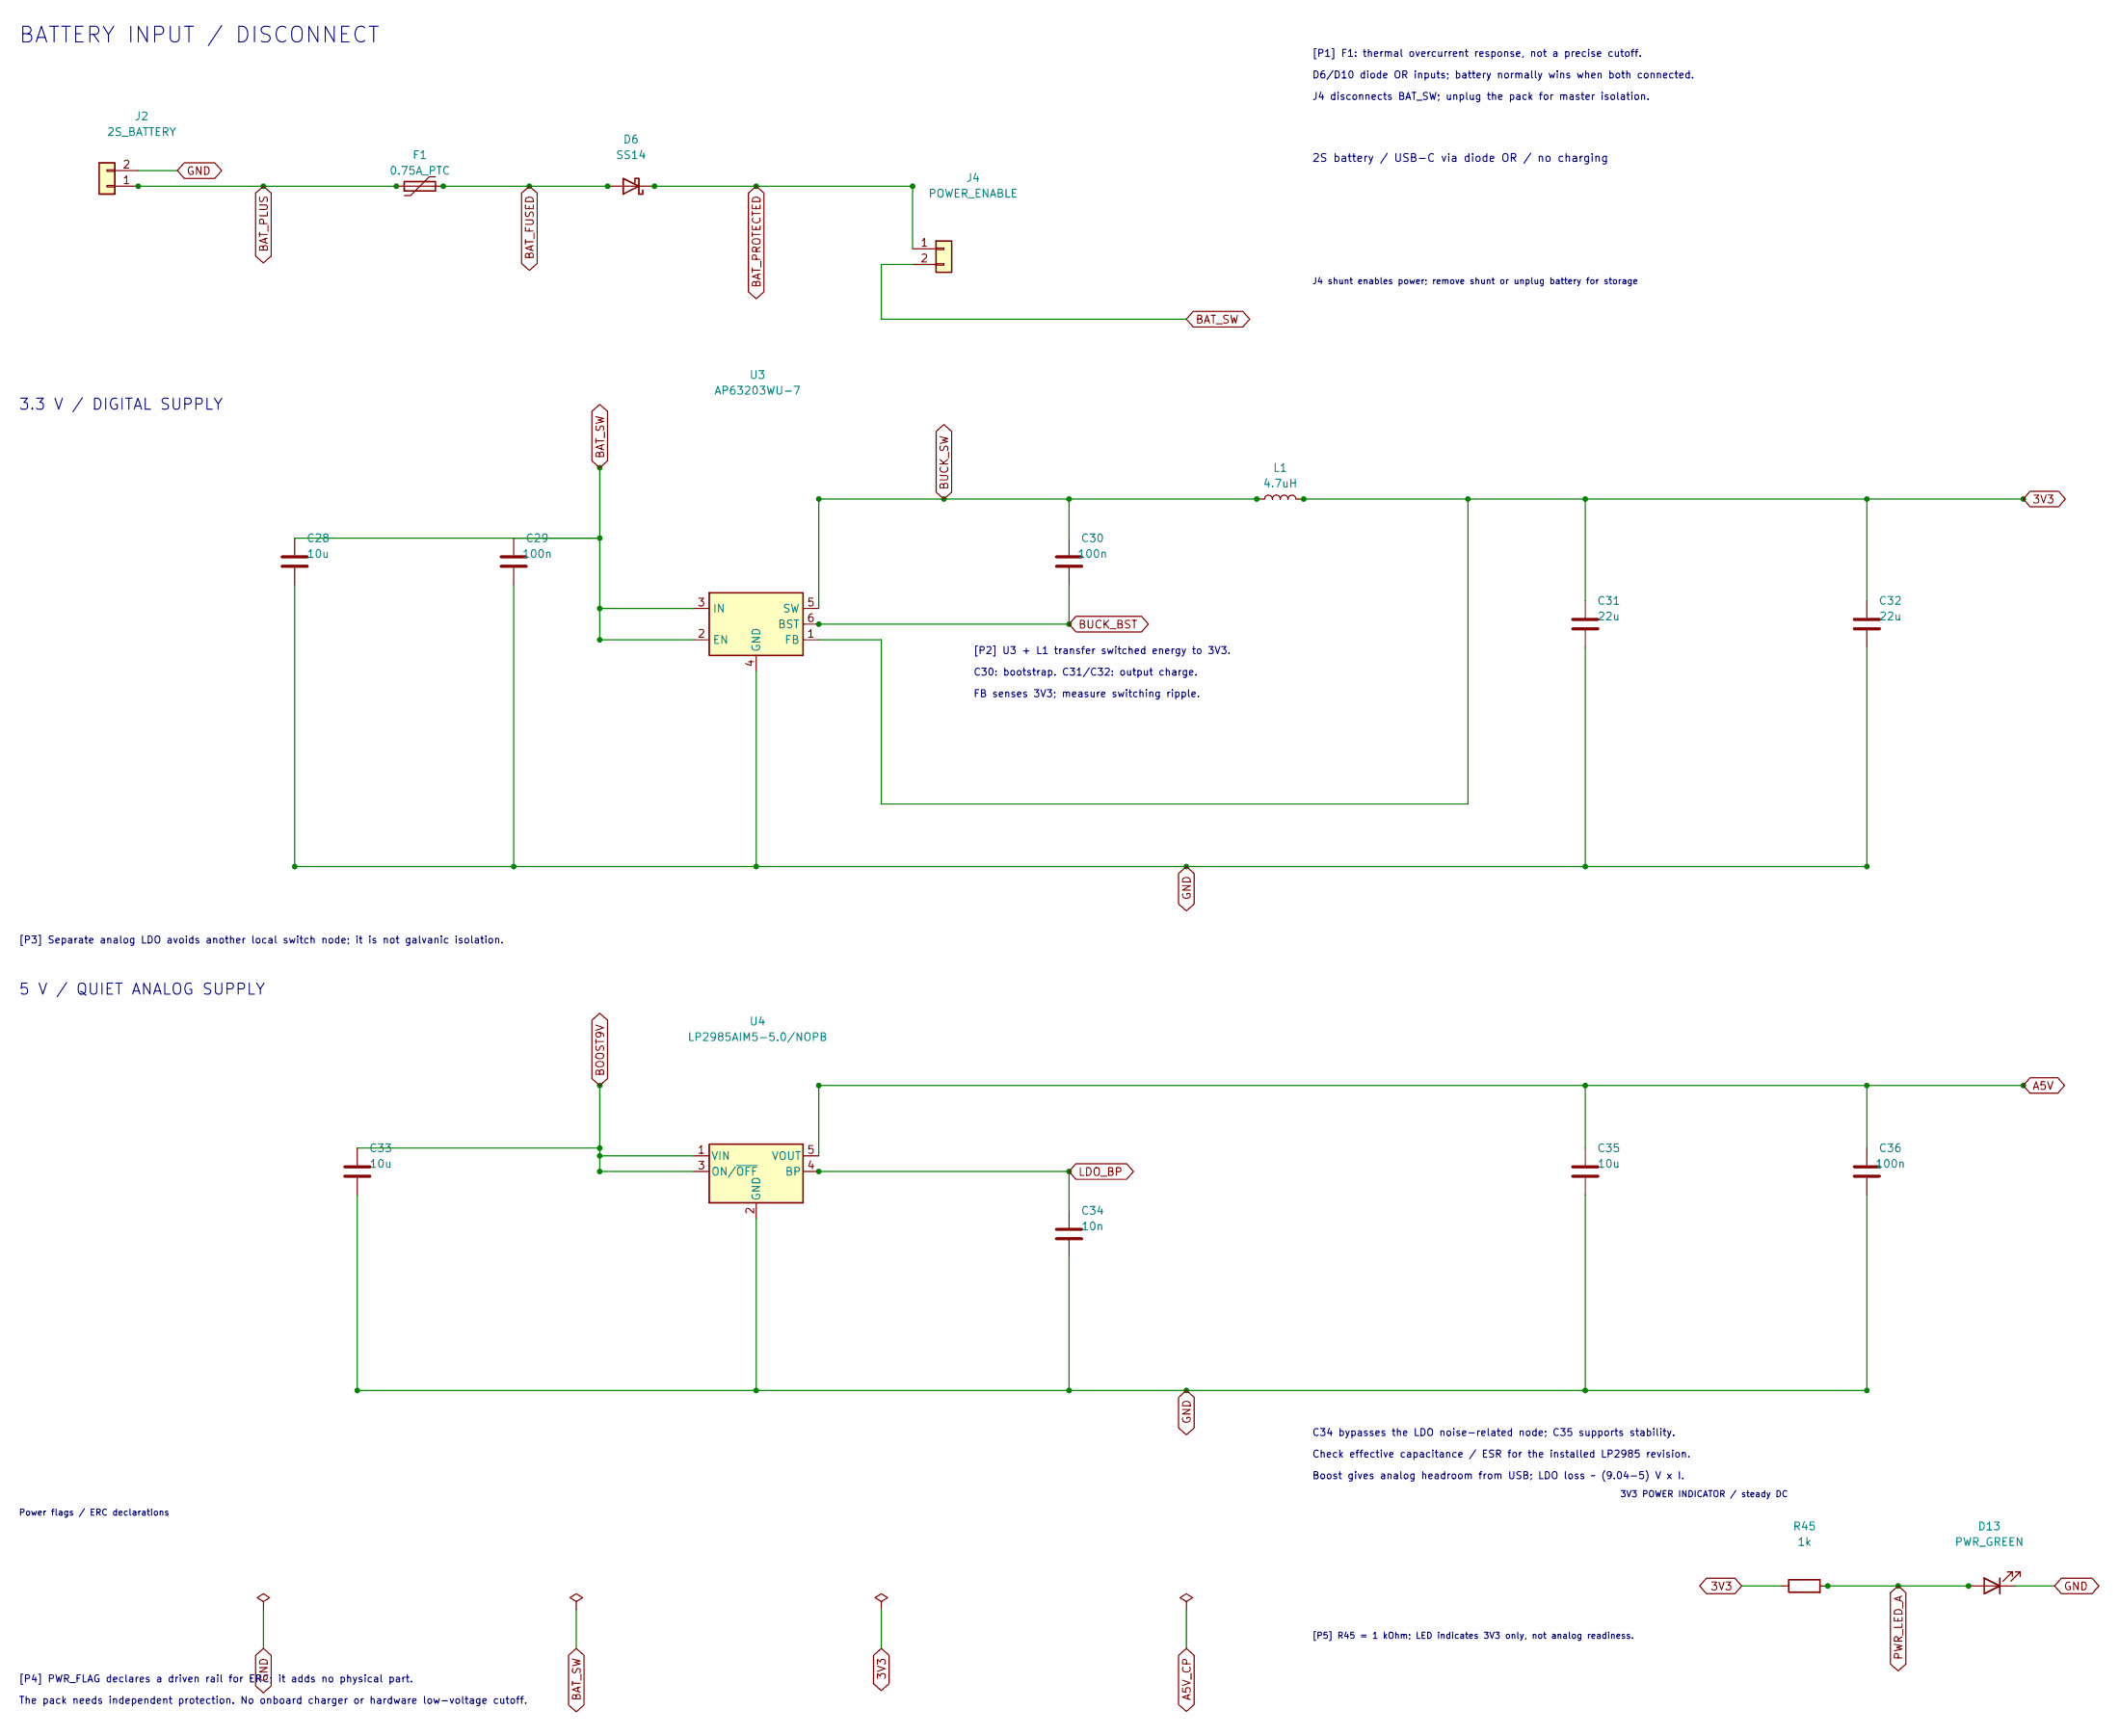
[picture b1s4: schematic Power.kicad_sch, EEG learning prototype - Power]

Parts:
C28, C33, C35: 10u; C_1206_3216Metric; MPN GRM31CR71C106KA12L
C29, C30, C36: 100n; C_0805_2012Metric; MPN GRM21BR71H104KA01L
C31, C32: 22u; C_1206_3216Metric; MPN GRM31CR61E226KE15L
C34: 10n; C_0805_2012Metric; MPN GRM21A5C1H103JA01D
D6: SS14; D_SMA; MPN SS14
D13: PWR_GREEN; LED_0805_2012Metric; MPN APT2012LZGCK
F1: 0.75A_PTC; Fuse_1812_4532Metric; MPN 1812L075/24DR
J2: 2S_BATTERY; JST_XH_B2B-XH-A_1x02_P2.50mm_Vertical; MPN B2B-XH-A
J4: POWER_ENABLE; PinHeader_1x02_P2.54mm_Vertical; MPN 61300211121
L1: 4.7uH; L_Bourns_SRP5030T; MPN SRP5030T-4R7M
R45: 1k; R_0805_2012Metric; MPN RC0805FR-071KL
U3: AP63203WU-7; TSOT-23-6; MPN AP63203WU-7
U4: LP2985AIM5-5.0/NOPB; SOT-23-5; MPN LP2985AIM5-5.0/NOPB

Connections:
3V3: C31.1, C32.1, L1.2, R45.1, U3.1 (FB); also elsewhere on the board
A5V: C35.1, C36.1, U4.5 (VOUT); also elsewhere on the board
BAT_FUSED: D6.2 (A), F1.2
BAT_PLUS: F1.1, J2.1
BAT_PROTECTED: D6.1 (K), J4.1; also elsewhere on the board
BAT_SW: C28.1, C29.1, J4.2, U3.2 (EN), U3.3 (IN); also elsewhere on the board
BOOST9V: C33.1, U4.1 (VIN), U4.3 (ON/~OFF); also elsewhere on the board
BUCK_BST: C30.1, U3.6 (BST)
BUCK_SW: C30.2, L1.1, U3.5 (SW)
GND: C28.2, C29.2, C31.2, C32.2, C33.2, C34.2, C35.2, C36.2, D13.1 (K), J2.2, U3.4 (GND), U4.2 (GND); also elsewhere on the board
LDO_BP: C34.1, U4.4 (BP)
PWR_LED_A: D13.2 (A), R45.2

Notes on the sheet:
BATTERY INPUT / DISCONNECT
2S battery / USB-C via diode OR / no charging
3.3 V / DIGITAL SUPPLY
5 V / QUIET ANALOG SUPPLY
Power flags / ERC declarations
3V3 POWER INDICATOR / steady DC
[P5] R45 = 1 kOhm; LED indicates 3V3 only, not analog readiness.
J4 shunt enables power; remove shunt or unplug battery for storage
[P1] F1: thermal overcurrent response, not a precise cutoff.
D6/D10 diode OR inputs; battery normally wins when both connected.
J4 disconnects BAT_SW; unplug the pack for master isolation.
[P2] U3 + L1 transfer switched energy to 3V3.
C30: bootstrap. C31/C32: output charge.
FB senses 3V3; measure switching ripple.
[P3] Separate analog LDO avoids another local switch node; it is not galvanic isolation.
C34 bypasses the LDO noise-related node; C35 supports stability.
Check effective capacitance / ESR for the installed LP2985 revision.
Boost gives analog headroom from USB; LDO loss ~ (9.04-5) V x I.
[P4] PWR_FLAG declares a driven rail for ERC; it adds no physical part.
The pack needs independent protection. No onboard charger or hardware low-voltage cutoff.
